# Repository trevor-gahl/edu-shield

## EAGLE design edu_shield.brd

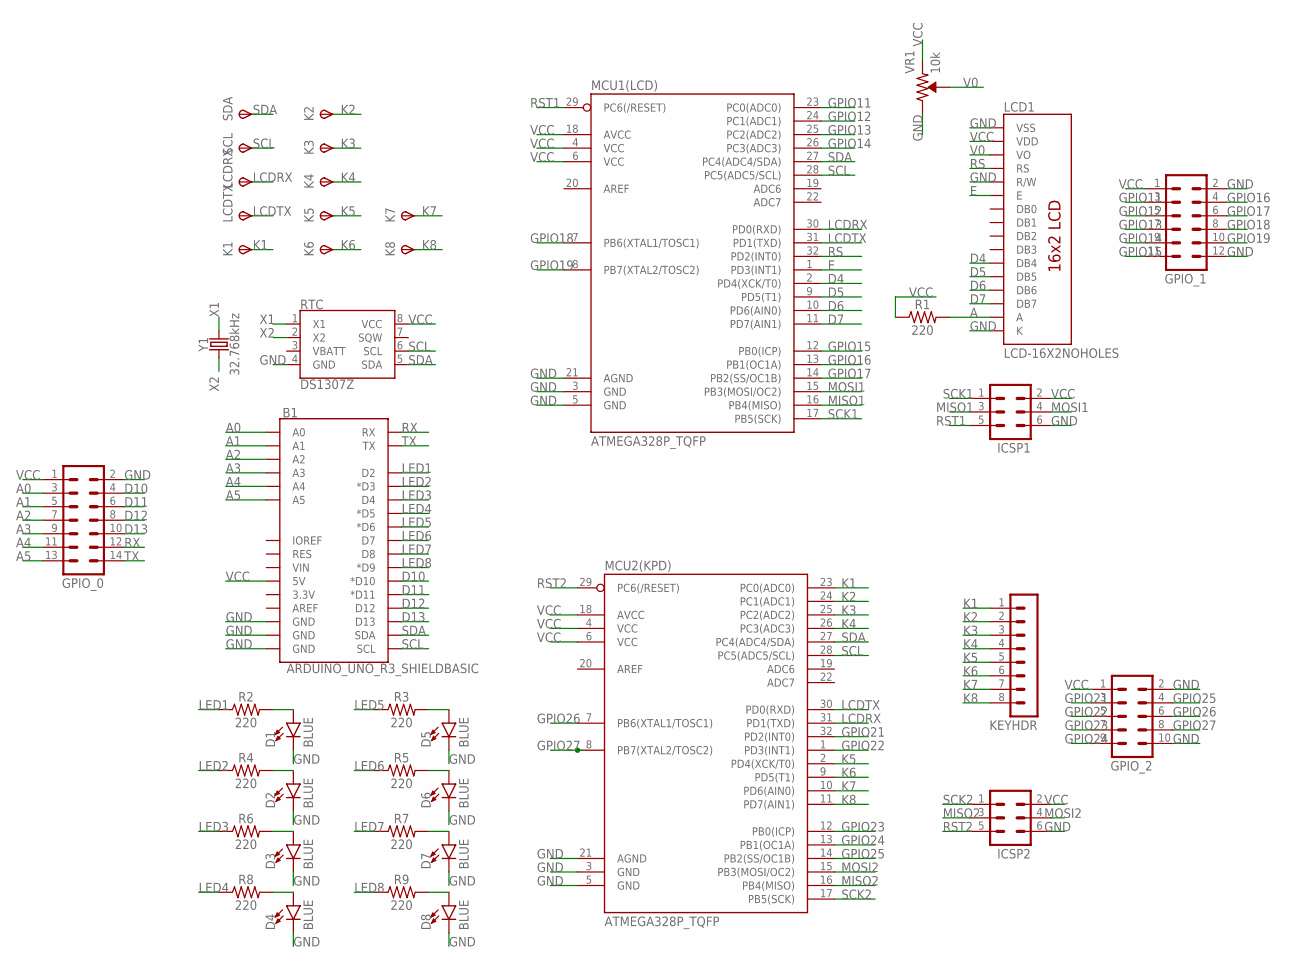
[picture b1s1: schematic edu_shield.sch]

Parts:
B1: ARDUINO_UNO_R3_SHIELDBASIC; UNO_R3_SHIELD
D1, D2, D3, D4, D5, D6, D7, D8: BLUE; LED-0603; MPN KPHD-1608LVVBC-D
GPIO_0: MA07-2
GPIO_1: MA06-2
GPIO_2: MA05-2
ICSP1, ICSP2: MA03-2
K1, K2, K3, K4, K5, K6, K7, K8: TPSTP06SQ; TP06SQ
KEYHDR: MA08-1
LCD1: LCD-16X2NOHOLES; LCD-16X2_NOHOLESNOSILK
LCDRX: TPSTP06SQ; TP06SQ
LCDTX: TPSTP06SQ; TP06SQ
MCU1(LCD), MCU2(KPD): ATMEGA328P_TQFP; TQFP32-08
R1, R2, R3, R4, R5, R6, R7, R8, R9: 220; 0603; MPN MC0603SAF2200T5E
RTC: DS1307Z; SO08-0.15; MPN DS1307Z+T&R
SCL: TPSTP06SQ; TP06SQ
SDA: TPSTP06SQ; TP06SQ
VR1: 10k; TRIMPOT-PTH-3386U; MPN 3296W-1-103LF
Y1: 32.768kHz; CRYSTAL-PTH-2X6-CYL; MPN AB38T-32.768KHZ

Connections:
A: LCD1.15 (A), R1.2
A0: B1.A0, GPIO_0.3
A1: B1.A1, GPIO_0.5
A2: B1.A2, GPIO_0.7
A3: B1.A3, GPIO_0.9
A4: B1.A4, GPIO_0.11
A5: B1.A5, GPIO_0.13
D4: LCD1.11 (DB4), MCU1(LCD).2 (PD4(XCK/T0))
D5: LCD1.12 (DB5), MCU1(LCD).9 (PD5(T1))
D6: LCD1.13 (DB6), MCU1(LCD).10 (PD6(AIN0))
D7: LCD1.14 (DB7), MCU1(LCD).11 (PD7(AIN1))
D10: B1.D10 (*D10), GPIO_0.4
D11: B1.D11 (*D11), GPIO_0.6
D12: B1.D12, GPIO_0.8
D13: B1.D13, GPIO_0.10
E: LCD1.6 (E), MCU1(LCD).1 (PD3(INT1))
GND: B1.GND@0 (GND), B1.GND@1 (GND), B1.GND@2 (GND), D1.C, D2.C, D3.C, D4.C, D5.C, D6.C, D7.C, D8.C, GPIO_0.2, GPIO_1.2, GPIO_1.12, GPIO_2.2, GPIO_2.10, ICSP1.6, ICSP2.6, LCD1.1 (VSS), LCD1.5 (R/W), LCD1.16 (K), MCU1(LCD).3 (GND), MCU1(LCD).5 (GND), MCU1(LCD).21 (AGND), MCU2(KPD).3 (GND), MCU2(KPD).5 (GND), MCU2(KPD).21 (AGND), RTC.4 (GND), VR1.3 (CW)
GPIO11: GPIO_1.3, MCU1(LCD).23 (PC0(ADC0))
GPIO12: GPIO_1.5, MCU1(LCD).24 (PC1(ADC1))
GPIO13: GPIO_1.7, MCU1(LCD).25 (PC2(ADC2))
GPIO14: GPIO_1.9, MCU1(LCD).26 (PC3(ADC3))
GPIO15: GPIO_1.11, MCU1(LCD).12 (PB0(ICP))
GPIO16: GPIO_1.4, MCU1(LCD).13 (PB1(OC1A))
GPIO17: GPIO_1.6, MCU1(LCD).14 (PB2(SS/OC1B))
GPIO18: GPIO_1.8, MCU1(LCD).7 (PB6(XTAL1/TOSC1))
GPIO19: GPIO_1.10, MCU1(LCD).8 (PB7(XTAL2/TOSC2))
GPIO21: GPIO_2.3, MCU2(KPD).32 (PD2(INT0))
GPIO22: GPIO_2.5, MCU2(KPD).1 (PD3(INT1))
GPIO23: GPIO_2.7, MCU2(KPD).12 (PB0(ICP))
GPIO24: GPIO_2.9, MCU2(KPD).13 (PB1(OC1A))
GPIO25: GPIO_2.4, MCU2(KPD).14 (PB2(SS/OC1B))
GPIO26: GPIO_2.6, MCU2(KPD).7 (PB6(XTAL1/TOSC1))
GPIO27: GPIO_2.8, MCU2(KPD).8 (PB7(XTAL2/TOSC2))
K1: K1.TP, KEYHDR.1, MCU2(KPD).23 (PC0(ADC0))
K2: K2.TP, KEYHDR.2, MCU2(KPD).24 (PC1(ADC1))
K3: K3.TP, KEYHDR.3, MCU2(KPD).25 (PC2(ADC2))
K4: K4.TP, KEYHDR.4, MCU2(KPD).26 (PC3(ADC3))
K5: K5.TP, KEYHDR.5, MCU2(KPD).2 (PD4(XCK/T0))
K6: K6.TP, KEYHDR.6, MCU2(KPD).9 (PD5(T1))
K7: K7.TP, KEYHDR.7, MCU2(KPD).10 (PD6(AIN0))
K8: K8.TP, KEYHDR.8, MCU2(KPD).11 (PD7(AIN1))
LCDRX: LCDRX.TP, MCU1(LCD).30 (PD0(RXD)), MCU2(KPD).31 (PD1(TXD))
LCDTX: LCDTX.TP, MCU1(LCD).31 (PD1(TXD)), MCU2(KPD).30 (PD0(RXD))
LED1: B1.D2, R2.1
LED2: B1.D3 (*D3), R4.1
LED3: B1.D4, R6.1
LED4: B1.D5 (*D5), R8.1
LED5: B1.D6 (*D6), R3.1
LED6: B1.D7, R5.1
LED7: B1.D8, R7.1
LED8: B1.D9 (*D9), R9.1
MISO1: ICSP1.3, MCU1(LCD).16 (PB4(MISO))
MISO2: ICSP2.3, MCU2(KPD).16 (PB4(MISO))
MOSI1: ICSP1.4, MCU1(LCD).15 (PB3(MOSI/OC2))
MOSI2: ICSP2.4, MCU2(KPD).15 (PB3(MOSI/OC2))
unnamed: D1.A, R2.2
unnamed: D2.A, R4.2
unnamed: D3.A, R6.2
unnamed: D4.A, R8.2
unnamed: D8.A, R9.2
unnamed: D7.A, R7.2
unnamed: D6.A, R5.2
unnamed: D5.A, R3.2
RS: LCD1.4 (RS), MCU1(LCD).32 (PD2(INT0))
RST1: ICSP1.5, MCU1(LCD).29 (PC6(/RESET))
RST2: ICSP2.5, MCU2(KPD).29 (PC6(/RESET))
RX: B1.RX, GPIO_0.12
SCK1: ICSP1.1, MCU1(LCD).17 (PB5(SCK))
SCK2: ICSP2.1, MCU2(KPD).17 (PB5(SCK))
SCL: B1.SCL, MCU1(LCD).28 (PC5(ADC5/SCL)), MCU2(KPD).28 (PC5(ADC5/SCL)), RTC.6 (SCL), SCL.TP
SDA: B1.SDA, MCU1(LCD).27 (PC4(ADC4/SDA)), MCU2(KPD).27 (PC4(ADC4/SDA)), RTC.5 (SDA), SDA.TP
TX: B1.TX, GPIO_0.14
V0: LCD1.3 (VO), VR1.2 (WIPER)
VCC: B1.5V, GPIO_0.1, GPIO_1.1, GPIO_2.1, ICSP1.2, ICSP2.2, LCD1.2 (VDD), MCU1(LCD).4 (VCC), MCU1(LCD).6 (VCC), MCU1(LCD).18 (AVCC), MCU2(KPD).4 (VCC), MCU2(KPD).6 (VCC), MCU2(KPD).18 (AVCC), R1.1, RTC.8 (VCC), VR1.1 (CCW)
X1: RTC.1 (X1), Y1.2
X2: RTC.2 (X2), Y1.1

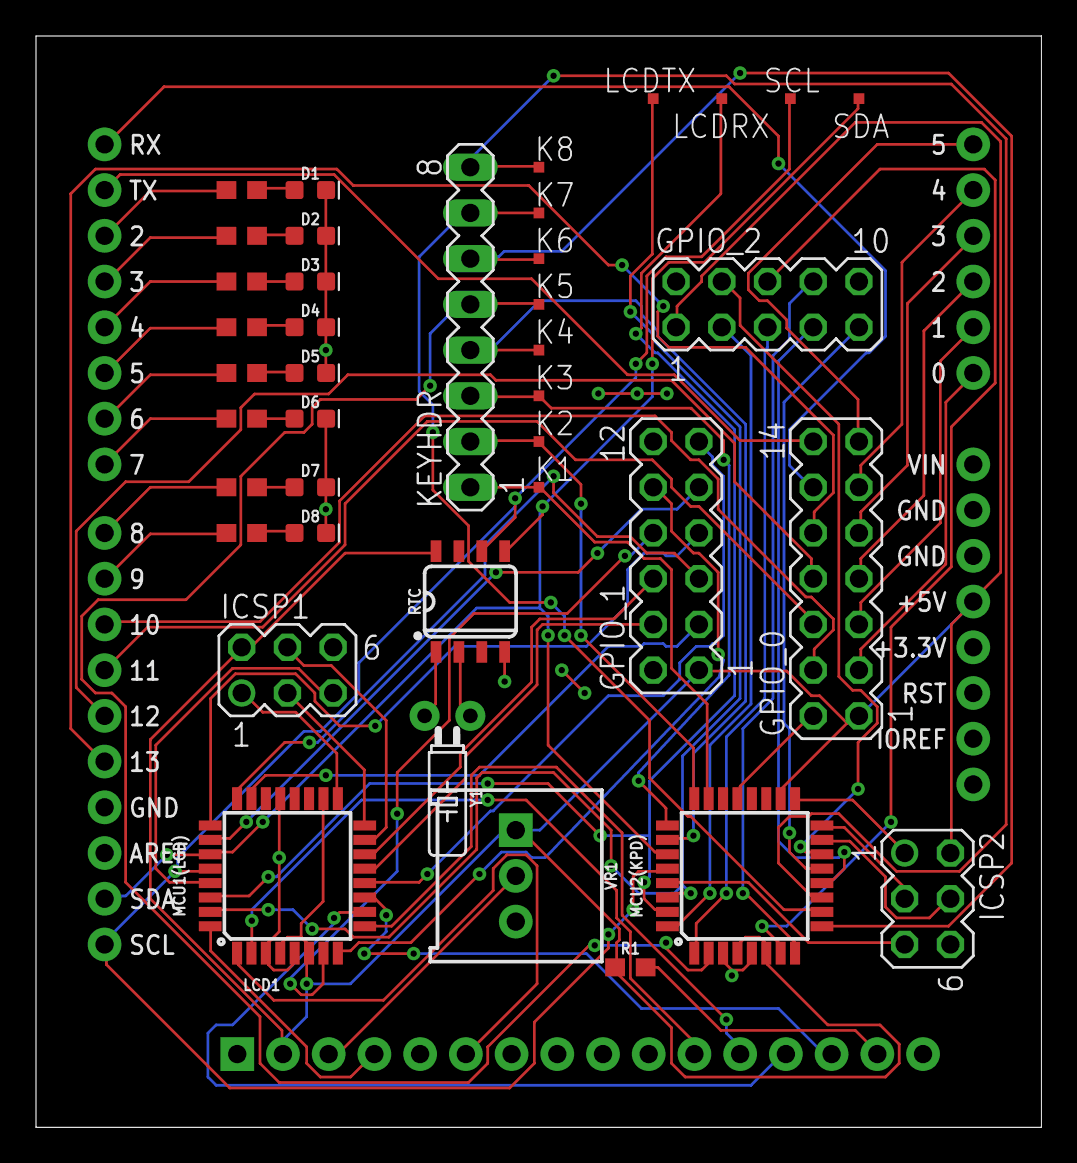
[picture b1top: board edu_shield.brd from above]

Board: 2 copper layers, 55.9 x 60.6 mm, 42 parts (0 on the bottom side), 76 nets.

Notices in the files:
parts and their libraries:
SparkFun-Boards: Licensing: Creative Commons ShareAlike 4.0 International - https://creativecommons.org/licenses/by-sa/4.0
